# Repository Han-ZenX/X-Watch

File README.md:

# X-Watch

X-Watch 是一款开源智能手表项目，主控芯片为 **STM32L4R9AII6U**，图形界面基于 **TouchGFX** 开发。本仓库统一管理硬件设计、嵌入式固件、配套软件、文档与测试。

> 项目处于早期开发阶段（硬件 Rev1.0），接口与目录结构可能随迭代调整。

## 核心方案

| 项目 | 选型 |
|------|------|
| 主控 MCU | STM32L4R9AII6U（Arm Cortex-M4F，120 MHz，2 MB Flash，640 KB SRAM，UFBGA169） |
| 图形框架 | TouchGFX（配合 TouchGFX Designer 设计界面） |
| 图形加速 | Chrom-ART（DMA2D）、GFXMMU，显示接口可选 LTDC / MIPI DSI |
| 硬件 EDA | KiCad |
| 固件构建 | CMake + GCC ARM（arm-none-eabi） |
| 大文件管理 | Git LFS |

### 为什么选 STM32L4R9

- **超低功耗**：STM32L4+ 系列，适合电池供电的穿戴设备。
- **图形能力完整**：片上集成 LTDC、MIPI DSI Host、Chrom-ART 加速器和 GFXMMU（适合圆形屏帧缓冲），无需外置图形芯片。
- **TouchGFX 官方支持**：ST 提供 STM32L4R9I-DISCO 参考设计（圆形 AMOLED 屏），可作为软硬件起点，手册见 [docs/references/Rev1.0](docs/references/Rev1.0)。

## 目录结构

```
X-Watch/
├── firmware/      # 嵌入式固件（app / hal / drivers / services 四层架构）
├── hardware/      # 硬件设计（原理图、PCB、BOM、Gerber、3D、引脚表）
├── software/      # 配套软件（desktop / mobile / cloud）
├── tools/         # 构建脚本与辅助工具
├── docs/          # 项目文档
├── tests/         # 单元测试 / 集成测试 / 硬件在环测试
└── ci/            # CI/CD 流水线配置
```

完整的架构说明见 [docs/architecture/architecture.md](docs/architecture/architecture.md)。

## 快速开始

### 1. 获取代码

```bash
git lfs install
git clone git@github.com:Han-ZenX/X-Watch.git
```

### 2. 开发环境

- [STM32CubeMX](https://www.st.com/en/development-tools/stm32cubemx.html)：外设与时钟配置
- [TouchGFX Designer](https://www.st.com/en/development-tools/touchgfxdesigner.html)：UI 设计与代码生成
- GCC ARM 工具链（arm-none-eabi-gcc）、CMake ≥ 3.20、Ninja
- [KiCad](https://www.kicad.org/)：打开 `hardware/schematic/v1.0/XWatch_Rev1.0/` 下的工程
- 调试器：ST-LINK

### 3. 编译固件

```bash
cd firmware
cmake -B build -G Ninja -DBOARD=default
cmake --build build
```

或使用构建脚本：

```bash
python tools/scripts/build.py --board=default
```

## 硬件

- 原理图 / PCB：`hardware/schematic/v1.0/XWatch_Rev1.0/`（KiCad 工程）
- 引脚分配：[hardware/pinout/pinout.md](hardware/pinout/pinout.md)
- 每次硬件改版需同步更新引脚表与 `firmware/boards/` 下对应的板级配置。

## 开发计划

- [ ] 硬件 Rev1.0 原理图与 PCB 完成
- [ ] STM32L4R9 板级支持（时钟、电源、调试串口）
- [ ] 显示屏驱动与 TouchGFX 移植
- [ ] 触摸驱动接入
- [ ] 基础表盘与界面
- [ ] 低功耗管理

## 变更记录

见 [CHANGELOG.md](CHANGELOG.md)。

## 许可证

本项目基于 [MIT License](LICENSE) 开源。

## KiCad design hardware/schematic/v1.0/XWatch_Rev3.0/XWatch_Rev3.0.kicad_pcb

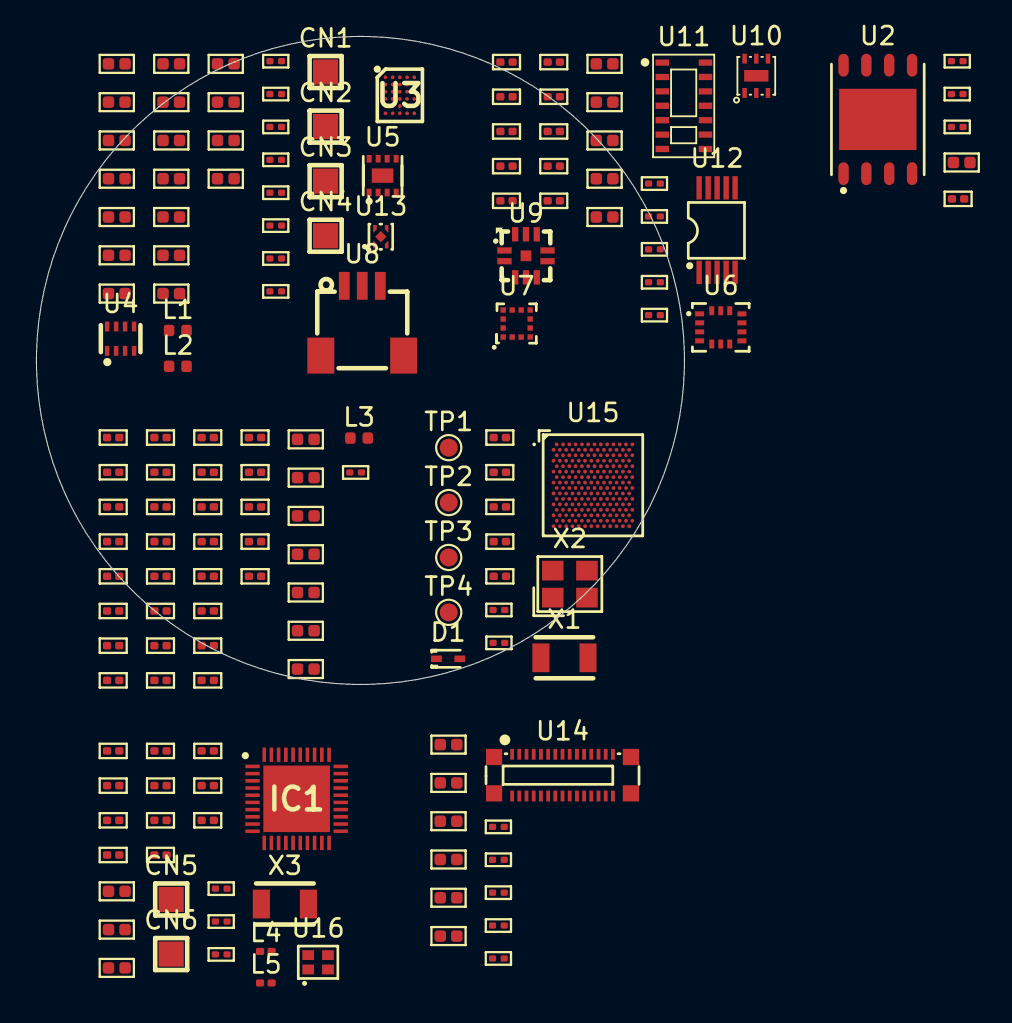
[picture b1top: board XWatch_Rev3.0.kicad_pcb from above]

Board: 2 copper layers, 36.0 x 36.0 mm, 158 parts (0 on the bottom side), 85 nets, no tracks yet.

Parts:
C1, C2, C86, C87: 5.6pF; GEN_C_0201
C3, C4: 10pF; GEN_C_0201
C5, C15, C71, C99: 4.7uF; GEN_C_0402
C6, C9, C10, C16, C17, C30, C59, C63, C78, C109: 10uF; GEN_C_0402
C7, C14, C49, C73, C75, C77: 100nF; GEN_C_0402
C8: 47nF; GEN_C_0402
C11, C12, C13, C104, C105: 2.2uF; GEN_C_0402
C18, C19, C61, C62, C64, C65, C66, C68, C74, C76, C80, C81, C101, C102: 1uF; GEN_C_0402
C20, C21, C22, C23, C24, C25, C26, C27, C28, C29, C48, C50, C51, C53, C54, C55, C56, C57, C58, C60, C67, C69, C70, C72, C79, C89, C90, C91, C92, C93, C94, C95, C96, C97, C98, C100, C103, C106, C107, C108, C110, C111, C112, C113: 100nF; GEN_C_0201
C52: 220nF; GEN_C_0201
C82: 1pF; GEN_C_0201
C83: 1.2pF; GEN_C_0201
C84, C85: 12pF; GEN_C_0201
C88: 100pF; GEN_C_0201
CN1, CN2, CN3, CN4, CN5, CN6: SCTA1A0100
D1: RB520S-30; RB520S-30_C7502701
IC1: nRF52833-QDAA-R; QFN40P500X500X90-41N
L1, L2, L3: 2.2uH; L_0402_1005Metric
L4: 4.7nH; L_0201_0603Metric
L5: 2.2nH; L_0201_0603Metric
R3, R17, R19, R26, R27, R28: 100K; GEN_R_0201
R4, R5, R13, R14: 4.7K; GEN_R_0201
R6, R7, R8, R15, R16, R18, R20, R21, R23, R24, R25: 10K; GEN_R_0201
R9: 24.9 k 1%; GEN_R_0201
R10: 38.3 k 1%; GEN_R_0201
R11, R12: 2.2K; GEN_R_0201
R22, R29: 0; GEN_R_0201
TP1, TP2, TP3, TP4: TestPoint; TestPoint_Pad_D1.0mm
U2: GD25LQ128EWIGR
U3: DA9168; BGA30C40P5X6_214X254X56
U4: TPS62840DLCR
U5: MAX17048G_T10
U6: LSM6DSOXTR
U7: LIS2MDLTR
U8: SM03B-SRSS-TB_LF_SN_P
U9: LPS27HHWTR
U10: OPT3001DNPR
U11: MAX30101EFD_T
U12: DRV2605LDGSR
U13: SK6018D4-33
U14: AXE530127-DO0143FMST02; AXE530127
U15: STM32U5A9BJY6QTR
U16: R832000033-32MHZ; R832000033
X1, X3: 32.768KHZ; NX3215SA_32_768KHZ_EXS00A-MU00525
X2: 16MHZ; TXM16M0004252CBCEO00T

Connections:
+1V8: C6.1, C20.1, C21.1, C22.1, C23.1, C24.1, C25.1, C26.1, C27.1, C28.1, C29.1, C30.1, C50.1, C51.1, C53.1, C54.1, C55.1, C56.2, C57.1, C60.1, C61.1, C67.2, C68.2, C71.1, C72.2, C75.2, C76.2, C79.2, C80.1, C89.1, C90.1, C91.1, C92.1, C93.1, C94.1, C95.1, C96.1, C97.1, C98.1, C99.1, C109.1, C110.1, C111.1, C112.1, IC1.8 (VDD_1), IC1.9 (VDDH), IC1.18 (VDD_2), IC1.30 (VDD_3), IC1.40 (VDD_4), L1.2, R4.1, R5.1, R6.1, R7.1, R11.1, R12.1, R13.1, R14.1, R15.1, R16.1, R18.1, R20.1, R21.1, R23.1, R24.1, R25.2, R28.2, R29.1, U2.8 (VCC), U4.8 (VOS), U6.5 (VDDIO), U6.8 (VDD), U6.12 (CS), U7.3 (CS), U7.9 (Vdd), U7.10 (Vdd_IO), U9.1 (Vdd_IO), U9.6 (CS), U9.10 (VDD), U10.1 (VDD), U11.11 (VDD), U14.25 (VDDIO), U15.A6 (VDD), U15.A12 (VDD), U15.A16 (VDDIO2), U15.A24 (VDD), U15.A26 (VDD), U15.B25 (VBAT), U15.E2 (VDDIO2), U15.F1 (VDD), U15.G2 (VDD), U15.G24 (VDDDSI), U15.H1 (VDD), U15.L2 (VDD), U15.L26 (VDD), U15.M1 (VDD), U15.N2 (VDD), U15.P1 (VDD), U15.R2 (VDD), U15.T1 (VDD), U15.T9 (VDDSMPS), U15.T15 (VDD), U15.T19 (VDD), U15.T25 (VDD)
+3V3: C66.1, C73.1, C74.1, C113.1, U13.1 (VOUT), U14.11 (TP_VCC), U14.23 (VCI_IN), U15.A2 (VDDUSB)
/BLE/DEC6: C81.1, IC1.26 (DEC6), IC1.38 (DEC4)
/BLE/nRESET: IC1.16 (P0.18/NRESET), R28.1
/MCU_IO/ALS_INT_N: R15.2, U10.5 (INT), U15.K21 (PF5)
/MCU_IO/BARO_INT: U9.7 (INT_DRDY), U15.L22 (PF10)
/MCU_IO/BLE_WAKE_MCU: IC1.17 (P0.20), R27.2, U15.D23 (PC13)
/MCU_IO/BLE_WAKE_NRF: IC1.7 (P0.11), R26.2, U15.T5 (PB12)
/MCU_IO/DSI_CK_N: U14.20 (MIPI_CLKN), U15.H25 (DSI_CKN)
/MCU_IO/DSI_CK_P: U14.18 (MIPI_CLKP), U15.G26 (DSI_CKP)
/MCU_IO/DSI_D0_N: U14.26 (MIPI_D0N), U15.F25 (DSI_D0N)
/MCU_IO/DSI_D0_P: U14.24 (MIPI_D0P), U15.E26 (DSI_D0P)
/MCU_IO/DSI_PWR_EN: U14.21 (PWR_EN), U15.C22 (PI5)
/MCU_IO/DSI_RESET: U14.19 (RESET), U15.E16 (PD5)
/MCU_IO/DSI_TE: U14.27 (TE), U15.N16 (PF11)
/MCU_IO/DSI_TP_INT: R20.2, U14.7 (TP_INT), U15.N14 (PE8)
/MCU_IO/DSI_TP_RESET: U14.9 (TP_RESET), U15.D21 (PI6)
/MCU_IO/HAPTIC_EN: R17.1, U12.5 (EN), U15.P17 (PF13)
/MCU_IO/I2C1.SCL: R4.2, U3.F5 (SCL), U5.7 (SCL), U15.C16 (PG14)
/MCU_IO/I2C1.SDA: R5.2, U3.E4 (SDA), U5.8 (SDA), U15.A14 (PG13)
/MCU_IO/I2C3.SCL: R12.2, U6.13 (SCL), U7.1 (SCL/SPC), U9.2 (SCL/SPC), U10.4 (SCL), U11.2 (SCL), U12.2 (SCL), U15.H15 (PH6)
/MCU_IO/I2C3.SDA: R11.2, U6.14 (SDA), U7.4 (SDA/SDI/SDO), U9.4 (SDA/SDI/SDO), U10.6 (SDA), U11.3 (SDA), U12.3 (SDA), U15.E12 (PH7)
/MCU_IO/I2C5.SCL: R14.2, U14.3 (TP_SCL), U15.F13 (PH5)
/MCU_IO/I2C5.SDA: R13.2, U14.5 (TP_SDA), U15.E10 (PH4)
/MCU_IO/IMU_INT1: U6.4 (INT1), U15.J16 (PF6)
/MCU_IO/IMU_INT2: U6.9 (INT2), U15.J14 (PF7)
/MCU_IO/MAG_DRDY: U7.7 (INT/DRDY/SDO), U15.L20 (PF9)
/MCU_IO/NRST: C48.1, TP3.1 (1_1), U15.M21 (NRST)
/MCU_IO/OSPI_CLK: U2.6 (SCLK), U15.M13 (PE10)
/MCU_IO/OSPI_IO0: U2.5 (SI(IO0)), U15.R14 (PE12)
/MCU_IO/OSPI_IO1: U2.2 (SO(IO1)), U15.N12 (PE13)
/MCU_IO/OSPI_IO2: R23.2, U2.3 (WP#(IO2)), U15.P13 (PE14)
/MCU_IO/OSPI_IO3: R25.1, U2.7 (HOLD#(IO3)), U15.R12 (PE15)
/MCU_IO/OSPI_NCS: R24.2, U2.1 (CS#), U15.P15 (PE11)
/MCU_IO/PPG_INT_N: R16.2, U11.13 (INT#), U15.T21 (PF12)
/MCU_IO/PWR_ALRT_N: R7.2, U5.5 (ALRT#), U15.C12 (PD3)
/MCU_IO/PWR_CHG_EN_N: R3.1, U3.E3 (CHG__EN_N), U15.D13 (PD2)
/MCU_IO/PWR_EN_3V3: R19.1, U13.3 (EN), U15.F15 (PD0)
/MCU_IO/PWR_INT_N: R6.2, U3.F4 (INT_N), U15.D15 (PD4)
/MCU_IO/PWR_RIN_N: C49.1, U3.D4 (RIN_N), U15.A10 (PD1)
/MCU_IO/SWCLK: TP2.1 (1_1), U15.D11 (PA14)
/MCU_IO/SWDIO: TP1.1 (1_1), U15.B3 (PA13)
/MCU_IO/USART3_CTS: IC1.14 (P0.15), U15.T7 (PB13)
/MCU_IO/USART3_RTS: IC1.15 (P0.17), U15.R6 (PB14)
/MCU_IO/USART3_RX: IC1.4 (P0.04/AIN2), U15.R10 (PB11)
/MCU_IO/USART3_TX: IC1.5 (P0.05/AIN3), U15.T13 (PB10)
/MCU_IO/USB_OTG_DM: CN3.1 (1_1), U15.C2 (PA11)
/MCU_IO/USB_OTG_DP: CN2.1 (1_1), U15.B1 (PA12)
/PWR/BAT_NTC: R9.2, R10.1, U3.D3 (TMP__SNS), U8.2 (NTC)
GND: C1.1, C2.1, C3.1, C4.2, C5.2, C6.2, C7.2, C9.2, C10.2, C11.2, C12.2, C13.2, C14.2, C15.2, C16.2, C17.2, C18.2, C19.2, C20.2, C21.2, C22.2, C23.2, C24.2, C25.2, C26.2, C27.2, C28.2, C29.2, C30.2, C48.2, C49.2, C50.2, C51.2, C52.2, C53.2, C54.2, C55.2, C56.1, C57.2, C58.2, C59.2, C60.2, C61.2, C62.2, C63.2, C64.1, C65.2, C66.2, C67.1, C68.1, C69.1, C70.2, C71.2, C72.1, C73.2, C74.2, C75.1, C76.1, C77.1, C78.1, C79.1, C80.2, C81.2, C82.2, C83.2, C84.1, C85.2, C86.1, C87.1, C88.2, C89.2, C90.2, C91.2, C92.2, C93.2, C94.2, C95.2, C96.2, C97.2, C98.2, C99.2, C100.2, C101.2, C102.2, C103.2, C104.2, C105.2, C106.2, C107.2, C108.2, C109.2, C110.2, C111.2, C112.2, C113.2, CN4.1 (1_1), CN6.1 (1_1), IC1.10 (VBUS), IC1.25 (VSS_PA), IC1.37 (VSS_1), IC1.41 (VSS_2), R3.2, R8.2, R10.2, R17.2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
unnamed: C3.2, X2.2
unnamed: C83.1, L4.2, L5.1
unnamed: CN5.1 (1_1), L5.2
unnamed: D1.2 (A), R18.2, U15.N22 (PA0)
unnamed: C82.1, IC1.24 (ANT), L4.1
unnamed: C69.2, IC1.1 (DEC1)
unnamed: C88.1, IC1.27 (DEC3)
unnamed: C70.1, IC1.21 (DEC5)
unnamed: C86.2, IC1.2 (P0.00/XL1), X3.1
unnamed: C87.2, IC1.3 (P0.01/XL2), X3.2
unnamed: C85.1, IC1.28 (XC1), U16.3
unnamed: C84.2, IC1.29 (XC2), U16.1
unnamed: C8.1, L2.1
unnamed: R9.1, U3.C5 (ILIMIT)
unnamed: C15.1, U3.C4 (REF)
unnamed: C8.2, U3.C3 (VBTS)
unnamed: C16.1, C17.1
unnamed: C12.1, U3.B5 (VOUT1)
unnamed: C13.1, U3.D5 (VOUT2)
unnamed: L1.1, U4.7 (SW)
unnamed: C52.1, U7.5 (C1)
unnamed: C64.2, U12.1 (REG)
unnamed: R21.2, U14.6 (CS)
unnamed: R22.2, U14.12 (SDO_SDI1)
unnamed: C100.1, C101.1, C102.1, C103.1, R29.2, U15.P25 (VREF+), U15.R26 (VDDA)
unnamed: L3.2, U15.T11 (VLXSMPS)
unnamed: C1.2, U15.C26 (PC14-OSC32_IN), X1.1
unnamed: C2.2, U15.D25 (PC15-OSC32_OUT), X1.2
unnamed: C4.1, U15.M23 (PH0-OSC_IN), X2.1 (OSC1)
unnamed: U15.M25 (PH1-OSC_OUT), X2.3 (OSC2)
unnamed: R8.1, U15.E20 (PH3-BOOT0)
VBAT: C7.1, C11.1, C14.1, C62.1, C63.1, U3.F3 (VBAT__SNS), U5.2 (CELL), U5.3 (VDD), U8.1 (BAT+), U12.6 (VDD/NC), U12.10 (VDD)
VBUS: C18.1, C19.1, CN1.1 (1_1), U3.A5 (VBUS__SNS)
VCORE: C104.1, C105.1, C106.1, C107.1, C108.1, L3.1, U15.A4 (VDD11), U15.A22 (VDD11), U15.D1 (VDD11USB), U15.J24 (VDD11DSI), U15.T3 (VDD11)
VSYS: C5.1, C9.1, C10.1, C58.1, C59.1, C65.1, C77.2, C78.2, L2.2, U4.2 (VIN), U4.4 (EN), U11.9 (VLED+), U11.10 (VLED+), U13.4 (VIN), U14.29 (VBAT), U14.30 (VBAT)

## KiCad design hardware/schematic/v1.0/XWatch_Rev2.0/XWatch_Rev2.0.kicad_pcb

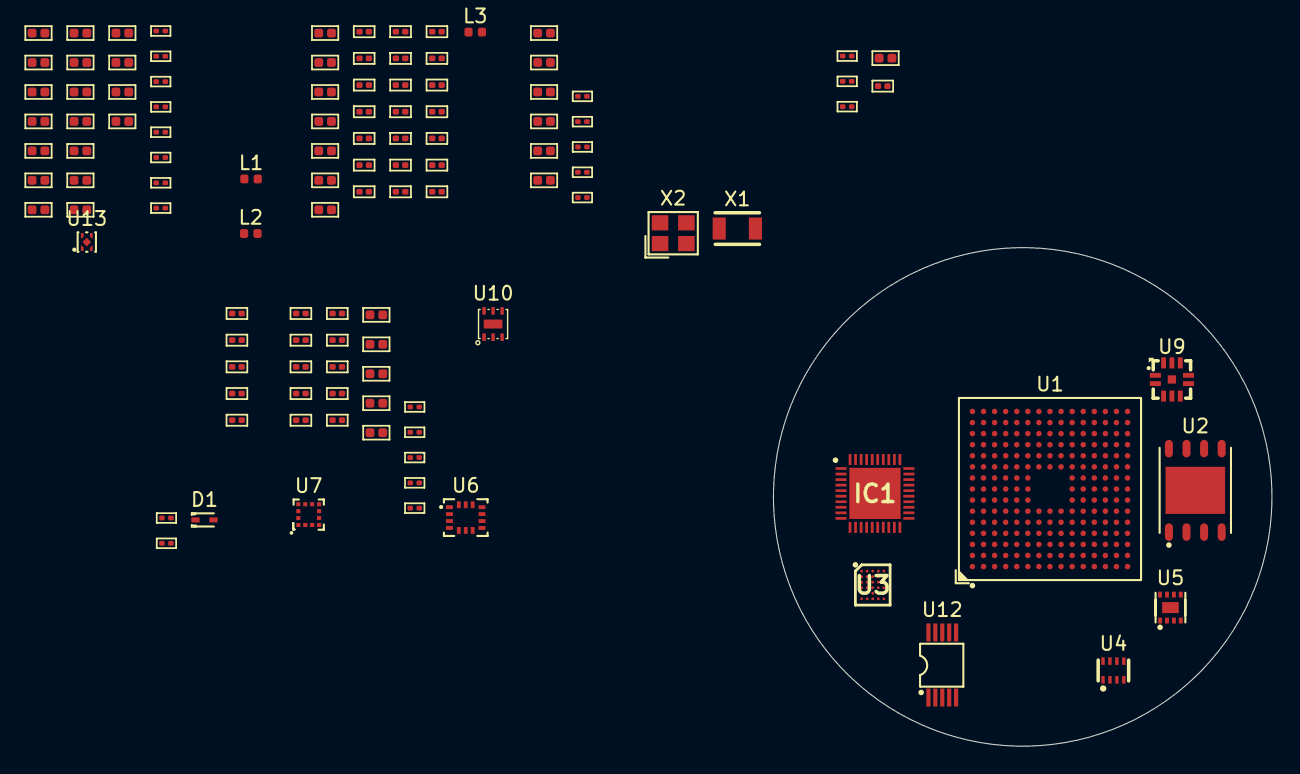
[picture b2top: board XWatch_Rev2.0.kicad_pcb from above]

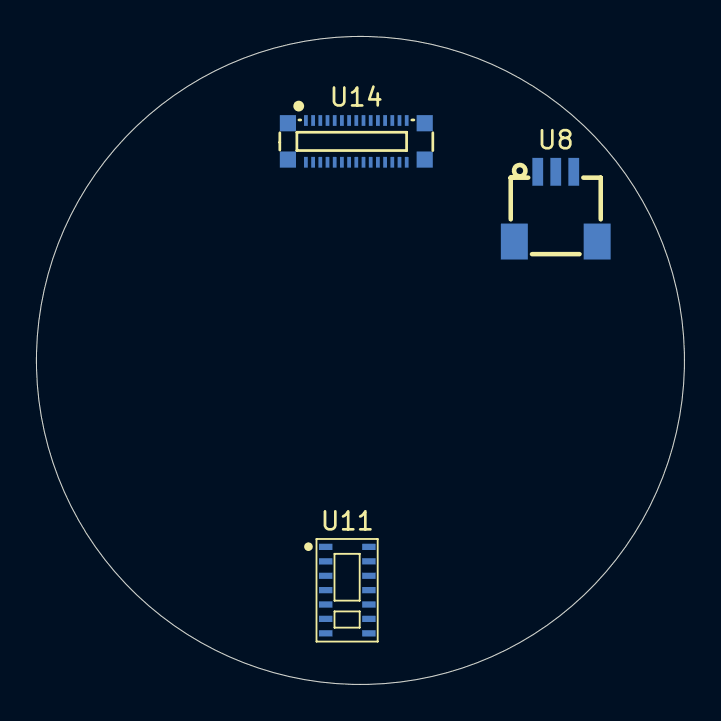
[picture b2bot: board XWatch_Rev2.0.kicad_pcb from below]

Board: 2 copper layers, 36.0 x 36.0 mm, 118 parts (3 on the bottom side), 48 nets, no tracks yet.

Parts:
C1, C2: 5.6pF; GEN_C_0201
C3, C4: 10pF; GEN_C_0201
C5, C15, C33: 4.7uF; GEN_C_0402
C6, C9, C10, C16, C17, C30, C46, C59, C63, C78: 10uF; GEN_C_0402
C7, C14, C49, C73, C75, C77: 100nF; GEN_C_0402
C8: 47nF; GEN_C_0402
C11, C12, C13, C41, C42: 2.2uF; GEN_C_0402
C18, C19, C34, C36, C61, C62, C64, C65, C66, C68, C74, C76: 1uF; GEN_C_0402
C20, C21, C22, C23, C24, C25, C26, C27, C28, C29, C31, C32, C35, C37, C38, C39, C40, C43, C44, C45, C47, C48, C50, C51, C53, C54, C55, C56, C57, C58, C60, C67: 100nF; GEN_C_0201
C52: 220nF; GEN_C_0201
D1: RB520S-30; RB520S-30_C7502701
IC1: nRF52833-QDAA-R; QFN40P500X500X90-41N
L1, L2, L3: 2.2uH; L_0402_1005Metric
R3, R17, R19: 100K; GEN_R_0201
R4, R5, R13, R14: 4.7K; GEN_R_0201
R6, R7, R8, R15, R16, R18, R20, R21, R23, R24, R25: 10K; GEN_R_0201
R9: 24.9 k 1%; GEN_R_0201
R10: 38.3 k 1%; GEN_R_0201
R11, R12: 2.2K; GEN_R_0201
R22: 0; GEN_R_0201
U1: STM32U5G9NJH6Q
U2: GD25LQ128EWIGR
U3: DA9168; BGA30C40P5X6_214X254X56
U4: TPS62840DLCR
U5: MAX17048G_T10
U6: LSM6DSOXTR
U7: LIS2MDLTR
U8: SM03B-SRSS-TB_LF_SN_P
U9: LPS27HHWTR
U10: OPT3001DNPR
U11: MAX30101EFD_T
U12: DRV2605LDGSR
U13: SK6018D4-33
U14: AXE530127-DO0143FMST02; AXE530127
X1: 32.768KHZ; NX3215SA_32_768KHZ_EXS00A-MU00525
X2: 16MHZ; TXM16M0004252CBCEO00T

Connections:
+1V8: C6.1, C20.1, C21.1, C22.1, C23.1, C24.1, C25.1, C26.1, C27.1, C28.1, C29.1, C30.1, C31.1, C32.1, C33.1, C38.1, C39.1, C40.1, C46.1, C47.1, C50.1, C51.1, C53.1, C54.1, C55.1, C56.2, C57.1, C60.1, C61.1, C67.2, C68.2, C75.2, C76.2, L1.2, R4.1, R5.1, R6.1, R7.1, R11.1, R12.1, R13.1, R14.1, R15.1, R16.1, R18.1, R20.1, R21.1, R23.1, R24.1, R25.2, U1.C2 (VBAT), U1.E8 (VDDIO2), U1.E9 (VDDUSB), U1.F5 (VDD), U1.F8 (VDD), U1.G5 (VDDDSI), U1.G11 (VDDIO2), U1.H11 (VDD), U1.J5 (VDD), U1.J11 (VDD), U1.K11 (VDD), U1.L7 (VDD), U1.L8 (VDD), U1.L9 (VDD), U1.L11 (VDD), U1.R12 (VDDSMPS), U2.8 (VCC), U4.8 (VOS), U6.5 (VDDIO), U6.8 (VDD), U6.12 (CS), U7.3 (CS), U7.9 (Vdd), U7.10 (Vdd_IO), U9.1 (Vdd_IO), U9.6 (CS), U9.10 (VDD), U10.1 (VDD), U11.11 (VDD), U14.25 (VDDIO)
+3V3: C66.1, C73.1, C74.1, U13.1 (VOUT), U14.11 (TP_VCC), U14.23 (VCI_IN)
/DSI_LCD/TP_INT: R20.2, U14.7 (TP_INT)
/DSI_LCD/TP_SCL: R14.2, U14.3 (TP_SCL)
/DSI_LCD/TP_SDA: R13.2, U14.5 (TP_SDA)
/MEMORY/OSPI_IO2: R23.2, U2.3 (WP#(IO2))
/MEMORY/OSPI_IO3: R25.1, U2.7 (HOLD#(IO3))
/MEMORY/OSPI_NCS: R24.2, U2.1 (CS#)
/PWR/BAT_NTC: R9.2, R10.1, U3.D3 (TMP__SNS), U8.2 (NTC)
/PWR/EN_3V3: R19.1, U13.3 (EN)
/PWR/FG_ALRT_N: R7.2, U5.5 (ALRT#)
/PWR/PWR_CHG_EN_N: R3.1, U3.E3 (CHG__EN_N)
/PWR/PWR_INT_N: R6.2, U3.F4 (INT_N)
/PWR/PWR_RIN_N: C49.1, U3.D4 (RIN_N)
/PWR/PWR_SCL: R4.2, U3.F5 (SCL), U5.7 (SCL)
/PWR/PWR_SDA: R5.2, U3.E4 (SDA), U5.8 (SDA)
/SENSOR/ALS_INT_N: R15.2, U10.5 (INT)
/SENSOR/DRV_REG: C64.2, U12.1 (REG)
/SENSOR/HAPTIC_EN: R17.1, U12.5 (EN)
/SENSOR/MAG_C1: C52.1, U7.5 (C1)
/SENSOR/PPG_INT_N: R16.2, U11.13 (INT#)
/SENSOR/SENSOR_SCL: R12.2, U6.13 (SCL), U7.1 (SCL/SPC), U9.2 (SCL/SPC), U10.4 (SCL), U11.2 (SCL), U12.2 (SCL)
/SENSOR/SENSOR_SDA: R11.2, U6.14 (SDA), U7.4 (SDA/SDI/SDO), U9.4 (SDA/SDI/SDO), U10.6 (SDA), U11.3 (SDA), U12.3 (SDA)
GND: C1.1, C2.1, C3.1, C4.2, C5.2, C6.2, C7.2, C9.2, C10.2, C11.2, C12.2, C13.2, C14.2, C15.2, C16.2, C17.2, C18.2, C19.2, C20.2, C21.2, C22.2, C23.2, C24.2, C25.2, C26.2, C27.2, C28.2, C29.2, C30.2, C31.2, C32.2, C33.2, C34.2, C35.2, C36.2, C37.2, C38.2, C39.2, C40.2, C41.2, C42.2, C43.2, C44.2, C45.2, C46.2, C47.2, C48.2, C49.2, C50.2, C51.2, C52.2, C53.2, C54.2, C55.2, C56.1, C57.2, C58.2, C59.2, C60.2, C61.2, C62.2, C63.2, C64.1, C65.2, C66.2, C67.1, C68.1, C73.2, C74.2, C75.1, C76.1, C77.1, C78.1, R3.2, R8.2, R10.2, R17.2, R19.2, R22.1, U1.A1 (VSS), U1.A15 (VSS), U1.E10 (VSS), U1.F6 (VSS), U1.F7 (VSS), U1.F9 (VSS), U1.F10 (VSS), U1.G6 (VSSDSI), U1.G10 (VSS), U1.H2 (VSSDSI), U1.H6 (VSSDSI), U1.H10 (VSS), U1.H15 (VSS), U1.J2 (VSSDSI), U1.J6 (VSS), U1.J10 (VSS), U1.J15 (VSS), U1.K5 (VREFM), U1.K6 (VSSA), U1.K7 (VSS), U1.K8 (VSS), U1.K9 (VSS), U1.K10 (VSS), U1.L10 (VSS), U1.P12 (VSSSMPS), U1.R1 (VSS)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
unnamed: C3.2, X2.2
unnamed: D1.2 (A), R18.2, U1.N4 (PA0-WKUP1)
unnamed: C34.1, C35.1, C36.1, C37.1, U1.L5 (VREFP), U1.L6 (VDDA)
unnamed: L3.2, U1.R11 (VLXSMPS)
unnamed: C48.1, U1.R2 (NRST)
unnamed: C2.2, U1.B1 (PC14-OSC32_IN), X1.2
unnamed: C1.2, U1.C1 (PC15-OSC32_OUT), X1.1
unnamed: U1.N1 (PH0-OSC_IN), X2.3 (OSC2)
unnamed: C4.1, U1.N2 (PH1-OSC_OUT), X2.1 (OSC1)
unnamed: R8.1, U1.B4 (PH3-BOOT0)
unnamed: C8.1, L2.1
unnamed: R9.1, U3.C5 (ILIMIT)
unnamed: C15.1, U3.C4 (REF)
unnamed: C8.2, U3.C3 (VBTS)
unnamed: C16.1, C17.1
unnamed: C12.1, U3.B5 (VOUT1)
unnamed: C13.1, U3.D5 (VOUT2)
unnamed: L1.1, U4.7 (SW)
unnamed: R21.2, U14.6 (CS)
unnamed: R22.2, U14.12 (SDO_SDI1)
VBAT: C7.1, C11.1, C14.1, C62.1, C63.1, U3.F3 (VBAT__SNS), U5.2 (CELL), U5.3 (VDD), U8.1 (BAT+), U12.6 (VDD/NC), U12.10 (VDD)
VBUS: C18.1, C19.1, U3.A5 (VBUS__SNS)
VDD11: C41.1, C42.1, C43.1, C44.1, C45.1, L3.1, U1.E6 (VDD11), U1.E11 (VDD11), U1.F11 (VDD11USB), U1.H5 (VDD11DSI), U1.R13 (VDD11)
VSYS: C5.1, C9.1, C10.1, C58.1, C59.1, C65.1, C77.2, C78.2, L2.2, U4.2 (VIN), U4.4 (EN), U11.9 (VLED+), U11.10 (VLED+), U13.4 (VIN), U14.29 (VBAT), U14.30 (VBAT)

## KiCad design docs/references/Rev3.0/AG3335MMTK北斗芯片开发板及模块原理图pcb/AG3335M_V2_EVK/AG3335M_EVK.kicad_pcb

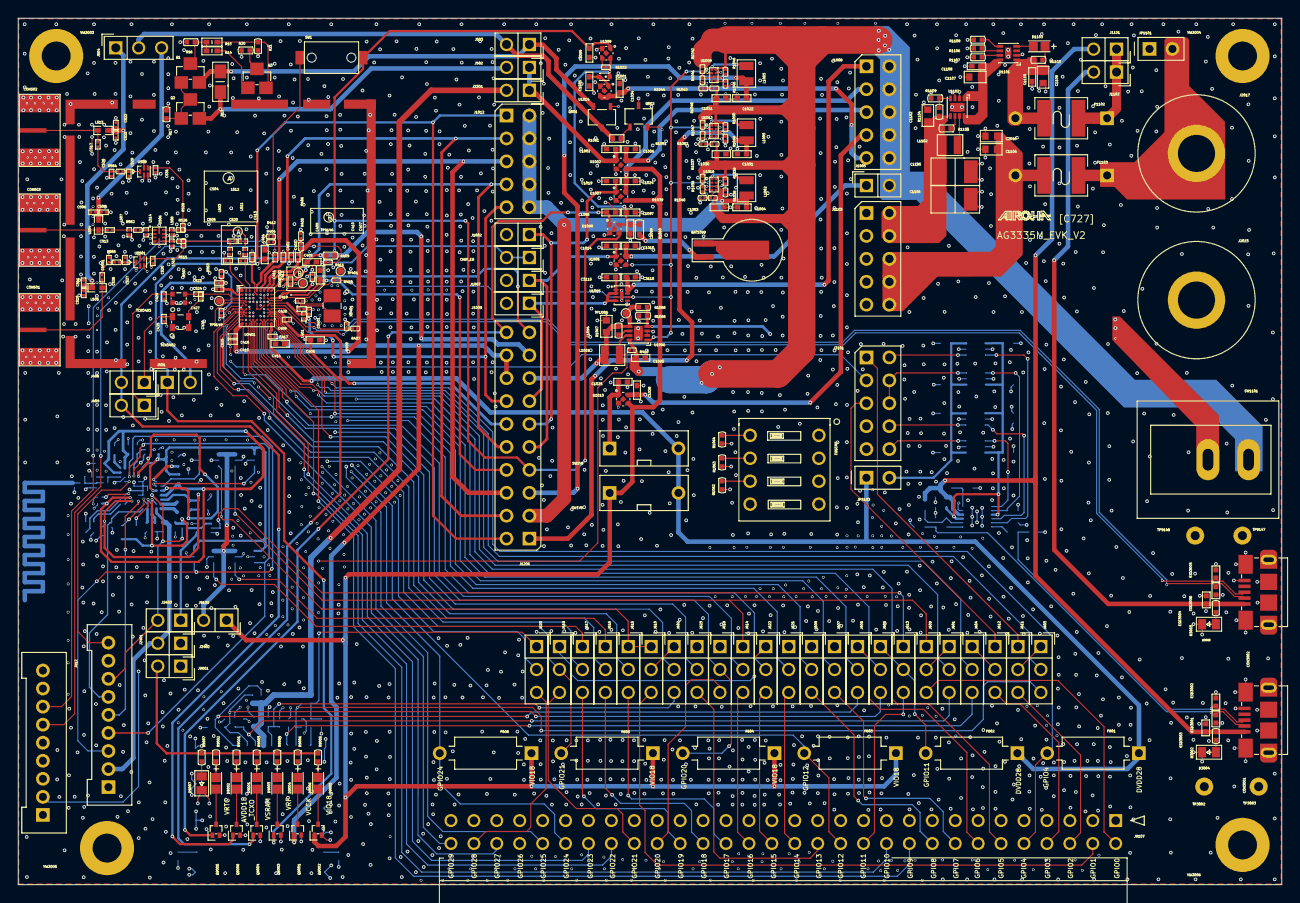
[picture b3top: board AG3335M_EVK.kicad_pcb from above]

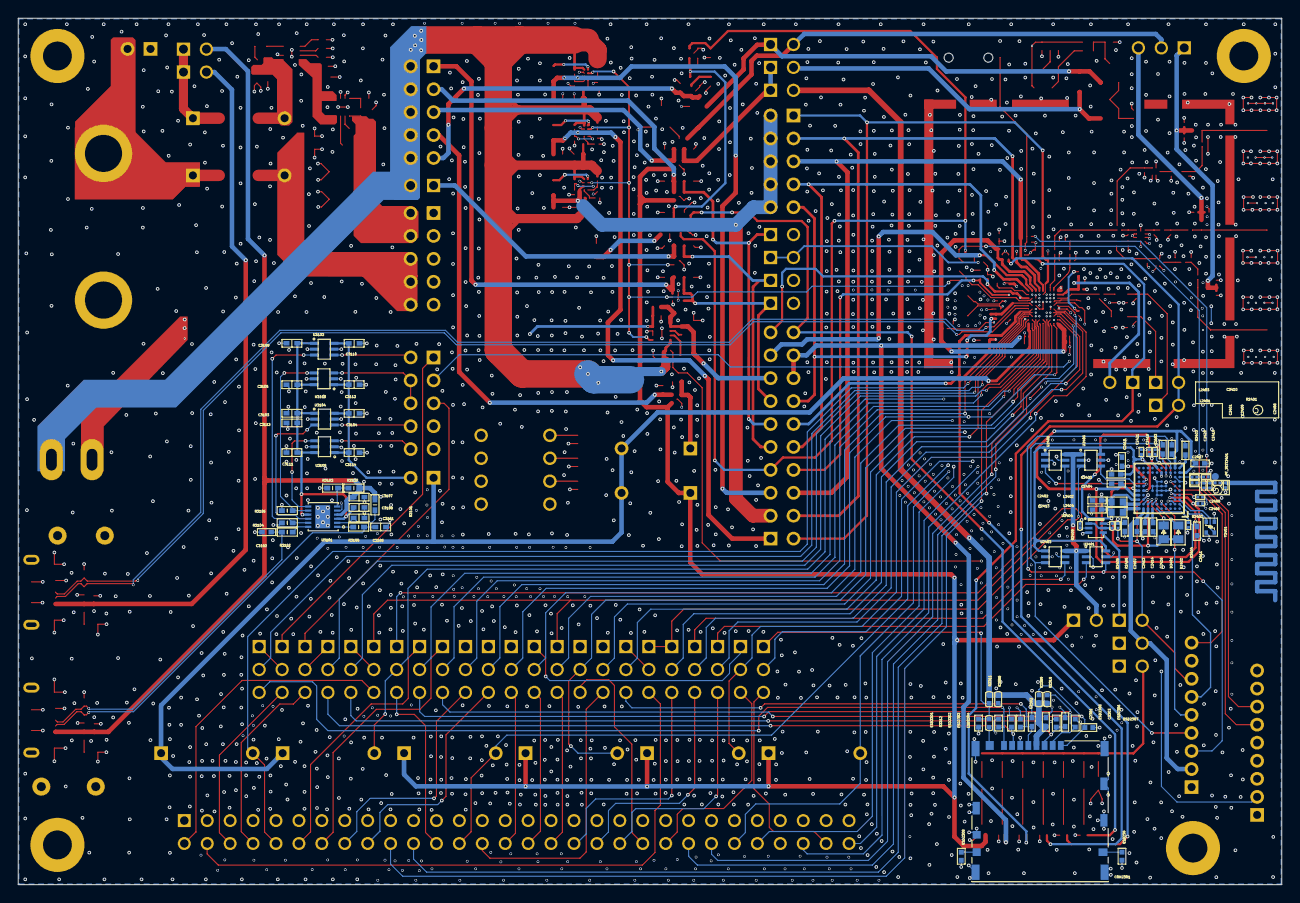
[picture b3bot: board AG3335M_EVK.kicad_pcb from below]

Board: 4 copper layers, 140.0 x 96.0 mm, 381 parts (86 on the bottom side), 241 nets.

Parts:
BAT1099: C0.22F3.3V$2F$SMD$2F$EN-RL
C0401, C402, C403, C407, C408, C409, C411, C412, C413, C415, C416, C417, C419, C420, C425, C426, C427, C428, C0501, C504, C505, C506, C508, C510, C511, C513, C517, C520, C521, C522, C523, C524, C525, C526, C527, C528, C529, C530, C531, C2401, C2405, C2406, C2408, C2409, C2410, C2418, C2421: C0201
C404, C405, C406, C410, C414, C1002, C1003, C1004, C1006, C1014, C1015, C1019, C1021, C1022, C1024, C1025, C1028, C1030, C1031, C1034, C1035, C1095, C1096, C1097, C1098, C1099, C1108, C1110, C2301, C2302, C2303, C2402, C2403, C2404, C2407, C2411, C2412, C2413, C2414, C2415, C2416, C2417, C2419, C2420, C3102, C3115, C3116: C0402
C1094, C1102, C1104, C1107, C1109, C2016: C0603
C1105, C1106: C1210
C3101, C3103, C3104, C3105, C3106, C3107, C3108, C3109, C3110, C3111, C3112, C3113, C3114: SC0402
CHIP_EN: DIP2$2F$P2.54
CON501, CON502, CON503: SMA8400M
CON2301: MICROSD$2F$8P$2F$SMD$2F$TA-M017-012-07-811
CON3001, CON3002: MICROUSB$2F$5P$2F$SMD$2F$P0.65$2F$R$2F$8791-N005-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; MICROUSB$2F$5P$2F$SMD$2F$P0.65$2F$R$2F$8791-N005-M1A0
D1001: D$2F$SMD$2F$VMD2
D1103, D9001, D9002, D9003, D9004, D9005, D9006: LED190
D2401, D2402, D3004, D3005, D9007: LED-S
ESD239, ESD2301, ESD2302, ESD2303, ESD2304, ESD2305, ESD2306, ESD2307, ESD2308, ESD3001, ESD3002, ESD3003, ESD3004, ESD3005, ESD3006: VR0402
F601, F602, F603, F604, F605, F606: R$5C$DIP
F1102, F1103: FUSE$2F$DIP$2F$SMD
J408, J409, J501, J502, J503, J1002, J1005, J1007, J1009, J1101, J1102, J2301, J2402, J2403, J9001, J9109: DIP2$2F$P2.54
J412, J2401: SIP-9P-2MM-FRAME
J504, J601, J602, J603, J604, J605, J606, J607, J608, J609, J610, J611, J612, J613, J614, J615, J616, J617, J618, J619, J620, J621, J622, J623: DIP3$2F$P2.54
J1008, J1012, J1103, J3101: HEADER10
J1206: HEADER10X2-P2.54
J2017, J2023: JACK$2F$BANAAA
J9107: DIP30X2$2F$P2.54$2F$R$2F$PHR230GB138
JP1101, JP3103: SIP-2P
L401, L503, L507, L508, L511, L512, L514, L515: L0201
L504, L505, L513: L$2F$IND$2F$SMD$2F$0402
L1001, L1102: L$2F$IND$2F$SMD$2F$2520
L1002, L1003, L1005: L$2F$IND$2F$SMD$2F$LQM2MP-0806
L2401, L2403: C0201
L2402, L2404: C0603_H300
PF_TEST2401: PADCB
Q1, Q2, Q3: SOT-23
Q501, Q502: SPP2301_USI
Q9001, Q9002, Q9003, Q9004, Q9005, Q9006: 2-1L1B$2F$SMD$2F$SSM3K35MFV
R13: R0805
R14, R15, R3101, R3102, R3103, R3104, R3105, R3106, R3107: SR0402
R16, R17, R20, R21, R409, R1062, R1063, R1064, R1065, R1067, R1068, R1103, R1104, R1105, R1106, R1107, R1108, R1109, R2308, R2309, R2310, R2311, R2312, R3002, R3003, R9001, R9002, R9003, R9004, R9005, R9006, R9007: R0402
R404, R405, R406, R407, R408, R410, R411, R412, R413, R507, R511, R526, R528, R552, R553, R554, R555, R1033, R1035, R1036, R1037, R1038, R1039, R1040, R1041, R1042, R1043, R1044, R1045, R1046, R1047, R1048, R1049, R1050, R1051, R1052, R2401, R2405, R2406, R2409: R0201
R1060: R0402$2F$SMD
R1061: 0402_USI
R2402, R2404: C0201
R2403: C0402
SHORT402: NC$2F$MMD$2F$L1$2F$4MIL
SW1: TS6301E180G
SW1V8, SW2V8: DIP-SWITCH_2X1
SW1101: SW2P$2F$DIP-V1
SW2002: SW8P_DIP_P2.54
TCXO402: TXCO4P$2F$SMD$2F$P0.4$2F$2.0X1.6$2F$KT2016K
TCXO403: TXCO4P$2F$SMD$2F$P0.4$2F$1.65X1.25$2F$1612TCXO
TP401, TP1001, TP9146, TP9149: TP30MIL
TP3002, TP3003, TP9147, TP9148: HOLE$2F$PTH$2F$D1R2
U0401: AG3335M_3.8X4.2(R9XC10)-0.4BPAA
U0501, U509: SAW-1.1X0.9
U506: SAW1511
U1002, U1005, U1007, U1010, U1014, U1098, U1099: ZQFN-4L-1X1
U1008, U1012, U1016: WL-CSP0.9X1.6-8
U1015: XDFN8-P0.4-1.6X1.2
U1096, U1102: WDFN8$2F$SMD$2F$P0.5$2F$RT5715
U1101: WDFN8$2F$SMD$2F$P0.5$2F$RT9718
U2401, U2403, U2405, U2406, U3102, U3103, U3104, U3105: SOT363-6PIN
U2402: BGA76-5.5X5.5-AHT
U2404: EMT6-P0.5
U3101: DFN12
VIA3003, VIA3004, VIA3005, VIA3006: TH3MM
X0401: RTC3215
Y2401: XT2016

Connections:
1V8_LDO: C1004.1, J1012.2, J1012.4, J1012.6, J1012.8, J1012.10, J1206.3, L1002.2, U1016.C2
2V8_LDO: C1025.1, SW2V8.1, U1010.1
3V1_LDO_RTC: C1035.1, D1001.1, U1014.1
3V3_LDO_ANT: J503.1, Q1.2, Q501.2, R13.2
3V3_LDO_IC: C1002.1, J502.1, J2301.1, U1002.1
3V3_LDO_RF: J502.2, Q2.2, R13.1
3V3_LDO_SD: C2301.1, CON2301.4, J2301.2, R2308.2, R2309.2, R2310.2, R2311.1
AD_IN: C1102.1, C1105.1, C1106.1, J1103.2, J1103.4, L1102.2, R1104.1, R1105.2, U1102.5
AD_IN_FB: R1104.2, R1109.1, U1102.4
AD_IN_PG: R1105.1, U1102.6
AD_IN_PIN: C1107.1, C1108.1, U1101.8, U1102.1, U1102.8
AG3335_GPIO0_O: J609.3, J9107.2
AG3335_GPIO1_O: J610.3, J9107.4
AG3335_GPIO2_O: J611.3, J9107.6
AG3335_GPIO3_O: J612.3, J9107.8
AG3335_GPIO4_O: F601.2, J9107.10
AG3335_GPIO5_O: J605.1, J9107.12
AG3335_GPIO6_O: J606.1, J9107.14
AG3335_GPIO7_O: J607.3, J9107.16
AG3335_GPIO8_O: J608.3, J9107.18
AG3335_GPIO11: F602.2, J613.2
AG3335_GPIO11_O: J613.3, J9107.24
AG3335_GPIO12_O: F603.2, J9107.26
AG3335_GPIO13_O: J623.3, J9107.28
AG3335_GPIO14_O: J621.3, J9107.30
AG3335_GPIO15_O: J622.3, J9107.32
AG3335_GPIO16_O: J614.3, J9107.34
AG3335_GPIO17_O: J615.3, J9107.36
AG3335_GPIO18_O: J616.3, J9107.38
AG3335_GPIO19_O: J617.3, J9107.40
AG3335_GPIO20: F604.2, J618.2
AG3335_GPIO20_O: J618.3, J9107.42
AG3335_GPIO21: F605.2, J619.2
AG3335_GPIO21_O: J619.3, J9107.44
AG3335_GPIO24_O: F606.2, J9107.50
AG3335_GPIO26_O: J3101.3, J9107.54
AG3335_GPIO28_O: J620.3, J9107.58
ANTENNA_BIAS: J618.1, J623.1, Q501.1
ANT_DETECT: J621.1, Q3.2, R15.2, R21.2
AVDD07_DCXO: C525.1, R553.1
AVDD07_L1_L5: C523.1, C524.1, J501.2, R553.2
AVDD18_IN_IC: C412.1, J1012.3, J1206.4
AVDD18_TCXO: C402.1, J408.2, J409.2, Q9006.1
AVDD18_USB: C3115.1, J1009.1, J1206.13, U1015.1, U1015.2, U1015.4
AVDD18_USB_IC: C0401.1, L401.1
AVDD18_USB_L: J1012.9, J1206.14, L401.2
AVSS_AUXADC: C409.2, SHORT402.2
BATP: C2412.1, J2401.2, J2402.2, U2402.A9
BATP_35: J412.2, R410.1
BA_IN: C1104.1, C2016.1, F1103.2, J1103.6, J1103.8, J1103.10
BTEN: J613.1, R2409.1, R2409.2, U2404.2
BUCK_LV: C2413.1, C2418.1, L2404.2, U2402.E10, U2402.J5
BUCK_MV: C2402.1, C2411.1, L2402.2, U2402.B2, U2402.C10
CHIP_EN: CHIP_EN.1, CHIP_EN.2, R409.2, R411.2
COIN_BATTERY_IN: C1097.1, C1098.1, D1001.2, R1033.2, R1060.2, U1098.4, U1099.4
DVDD28_IO: C417.1, F601.1, F602.1, JP3103.1, SW1V8.2, SW2V8.2
EINT_ANTENNA: J619.1, J622.1, Q502.2
EXT_PWR_EN: R413.2, U1005.3, U1008.B1, U1012.B1, U1015.6, U1016.B1, U1096.1
EXT_PWR_EN_IC: R413.1, TP401.1
EXT_VCORE: C1094.1, J1206.15, L1001.2, R1067.2, R1068.1, TP1001.1, U1096.5
FSOURCE_D: R407.1, R408.2
FT234XD_CTS: R3104.2, U3101.11, U3102.3
FT234XD_RTS: R3106.2, U3101.8, U3103.4
FT234XD_RX: U3101.10, U3104.3
FT234XD_TX: U3101.7, U3105.4
FT234XD_VCCIO: C3103.2, C3106.2, C3108.1, C3109.2, C3111.2, C3113.2, U3101.3, U3101.9, U3102.1, U3103.6, U3104.1, U3105.6
GND_POWER: BAT1099.2, C0401.2, C402.2, C403.2, C404.2, C405.2, C406.2, C407.2, C408.2, C410.2, C411.2, C412.2, C413.2, C414.2, C415.2, C416.2, C417.2, C419.2, C420.2, C425.2, C428.2, C504.2, C505.2, C506.1, C508.2, C510.1, C511.2, C520.2, C521.1, C522.2, C523.2, C524.2, C525.2, C526.2, C527.2, C528.2, C529.2, C530.2, C531.2, C1002.2, C1003.2, C1004.2, C1006.2, C1014.2, C1015.2, C1019.2, C1021.2, C1022.2, C1024.2, C1025.2, C1028.2, C1030.2, C1031.2, C1034.2, C1035.2, C1094.2, C1095.2, C1096.2, C1097.2, C1098.2, C1099.2, C1102.2, C1104.2, C1105.2, C1106.2, C1107.2, C1108.2, C1109.2, C1110.2, C2016.2, C2301.2, C2302.2, C2303.2, C2401.1, C2402.2, C2403.1, C2404.1, C2405.1, C2406.1, C2407.1, C2408.2, C2409.1, C2410.1, C2411.2, C2412.2, C2413.2, C2414.2, C2415.1, C2416.2, C2417.1, C2418.2, C2419.1, C2420.1, C2421.2, C3101.2, C3102.2, C3103.1, C3104.1, C3105.1, C3106.1, C3107.1, C3108.2, C3109.1, C3110.1, C3111.1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
HV_MIC: C2416.1, U2402.A7
LDO_LV: C2415.2, U2402.G9
LDO_LV2: C2404.2, C2406.2, C2417.2, C2420.2, U2402.C2, U2402.D10, U2402.J1, U2402.K2
LED0: D2401.C, U2402.B8
LED1: D2402.C, U2402.B7
MSDC_SD_CLK_SD: C2302.1, CON2301.5, ESD2304.2, J602.3
MSDC_SD_CMD_SD: C2303.1, CON2301.3, ESD2305.2, J601.3
MSDC_SD_DAT0_SD: CON2301.7, ESD2303.2, J604.3
MSDC_SD_DAT1_SD: CON2301.8, ESD2302.2, J603.3, R2308.1
MSDC_SD_DAT2_SD: CON2301.1, ESD2307.2, J606.3, R2309.1
MSDC_SD_DAT3_SD: CON2301.2, ESD2306.2, J605.3, R2310.1
N51633: CON2301.9, ESD239.2
N52123: CON2301.12, R2312.1
N16794950: L1003.1, U1008.A1
N16795229: L1005.1, U1012.A1
N16854862: D9001.1, R9001.1
N16854864: J9001.2, R9001.2, R9002.2, R9003.2, R9004.2, R9005.2, R9006.2, R9007.2
N16854870: D9001.2, Q9006.3
N16854891: D9004.2, Q9003.3
N16854903: D9003.1, R9003.1
N16854911: D9005.2, Q9002.3
N16854913: D9006.1, R9006.1
N16854915: D9005.1, R9005.1
N16854917: D9002.1, R9002.1
N16854919: D9004.1, R9004.1
N16854923: D9002.2, Q9005.3
N16854939: D9003.2, Q9004.3
N16854943: D9006.2, Q9001.3
N16870677: L2402.1, U2402.B10
N16870742: C2405.2, U2402.D2
N16870865: L2404.1, U2402.A10
N17202749: C530.1, R507.2, U0501.4
N17206048: C504.1, L503.2, R507.1, R511.1
N17206944: C531.1, R528.1, U509.4
N17207071: L511.2, L512.1, R526.2, R528.2
N17484756: D3004.A, R3002.2
N17605947: C513.2, L507.1, R552.1
N17609220: L515.1, R511.2, U506.6
N17612681: C0501.2, C526.1, R555.2
N17616255: C517.2, C528.1, R554.2
N17980673: L508.1, R526.1, U506.9
N18225807: R3102.1, U3101.12
N18225821: R3103.2, R3107.2, U3101.6
N18225837: R3105.1, U3101.1
N18225847: C3101.1, R3101.2, U3101.2
N18232969: D1103.1, R1103.2
N18233257: L1102.1, U1102.7
N18234980: F1102.1, J1101.1, J1102.1
N18236556: J1103.1, J1103.3, J1103.5, J1103.7, J1103.9, SW1101.1
N18250230: C2408.1, R2401.1
N18250379: C2410.2, L2403.2
N18285237: L514.1, R552.2, U506.1
N18322393: R2405.1, U2404.1, U2404.5
N18322505: J2403.1, U2404.4
N18335230: R1033.1, U1099.3
N18349170: BAT1099.1, R1060.1
N18407213: D3005.A, R3003.2
N18420282: F1103.1, J2017.1, JP1101.2
N18427771: C527.1, R555.1, U0501.1
N18429529: C529.1, R554.1, U509.1
N18461729: R1065.1, R1068.2, SW2002.1, SW2002.2, SW2002.3, U1096.4
N18461746: R1063.1, SW2002.6
N18461748: R1062.1, SW2002.7
N18461760: R1064.1, SW2002.5
N18461961: L1001.1, U1096.7
N18461975: R1067.1, U1096.6
N18466194: J601.1, J609.2
N18468488: J602.1, J610.2
N18468512: J603.1, J611.2
N18468536: J604.1, J612.2
N18508343: J412.7, R412.1
N18512158: Q1.1, Q2.1, Q2.3, R17.2
N18512190: Q1.3, R14.1, R15.1, R16.2
N18512210: Q3.1, R14.2
N18512260: Q3.3, R20.2
N18512651: J503.2, J504.2, Q501.3, R1061.1
N18512653: Q502.1, R1061.2
N18539579: L1002.1, U1016.A1
N184205860: D9007.A, R9007.1
OD_GPIO: J2401.5, U2402.B5
OSC_XIN: C426.1, C427.1
OVP_EN#: R1108.1, U1101.5
OVP_ILIM: R1107.1, U1101.7
OVP_VB: R1106.1, U1101.6
OVP_WRN#: D1103.2, U1101.4
PIO1: J2401.9, U2402.G2
PIO28: R2402.1, U2402.J4
PIO29: R2402.2, R2403.1, U2402.K4
PWR_PWR_EN: R404.2, R412.2, SW1.2
REGEN: J2401.7, J2403.2, R2406.1, U2402.C9
RF: C2401.2, C2409.2, L2401.2, PF_TEST2401.1, R2401.2
RF_IN_L1: C505.1, L503.1
RF_IN_L5: C520.1, L511.1
RF_P: L2401.1, L2403.1, U2402.H1
RST_N: J2401.6, R2404.2, U2402.A6
RST_N_35: J412.6, R411.1
RTC_XIN: C419.1, X0401.1
RTC_XOUT: C420.1, X0401.2
SDCD_SD_IC: ESD2301.2, J620.1, R2311.2, R2312.2
SYSTEM_PWRIN: C1109.1, C1110.1, F1102.2, R1103.1, U1101.1
TCXO_1612_VCC: C428.1, J409.1, TCXO403.4
TCXO_2016_VCC: C425.1, J408.1, TCXO402.4
TESTMODE: R405.1, R406.2
TXC_1612_OUT: C427.2, TCXO403.3
TXC_2016_OUT: C426.2, TCXO402.3
UART0_CTS: J612.1, J3101.5
UART0_RTS: J611.1, J3101.1
UART0_RX_AG3335: J412.4, J608.1, J3101.9
UART0_TX_AG3335: J412.3, J607.1, J3101.7
UART2_CTS: J610.1, J615.1, U2405.3
UART2_RTS: J609.1, J614.1, U2406.4
UART2_RX: J617.1, U2401.3
UART2_TX: J616.1, U2403.4
UART_CTS_AB1532: U2402.F9, U2406.3
UART_CTS_FT234: J3101.4, J3101.6, U3103.3
UART_RTS_AB1532: U2402.F10, U2405.4
UART_RTS_FT234: J3101.2, U3102.4
UART_RX_AB1532: J2401.4, U2402.J3, U2403.3
UART_RX_FT234: J3101.10, U3105.3
UART_TX_AB1532: J2401.3, U2401.4, U2402.K3
UART_TX_FT234: J3101.8, U3104.4
USB20_DM_AG3335: CON3002.2, ESD3006.2
USB20_DM_FT234XD: C3105.2, CON3001.2, ESD3001.2, R3105.2
USB20_DP_AG3335: CON3002.3, ESD3005.2
USB20_DP_FT234XD: C3102.1, CON3001.3, ESD3002.2, R3102.2
VAUXADC: C1014.1, J1007.1, J1206.9, U1005.1
VAUXADC_IC: C409.1, J1012.7, J1206.10
VBAT: C1003.1, C1021.1, C1030.1, C1095.1, J1005.2, J1008.2, J1008.4, J1008.6, J1008.8, J1008.10, J2402.1, J9001.1, R410.2, R1036.2, R1037.2, R1040.2, R1042.2, R1043.2, R1046.2, R1048.2, R1050.2, R1052.2, SW1101.2, U1008.A2, U1012.A2, U1016.A2, U1096.8
VBAT_1V8_ADC: C1015.1, J1005.1, U1005.4
VBAT_2V8: C1028.1, J1008.7, U1010.4
VBAT_3V1_RTC: C1034.1, J1008.9, U1014.3, U1014.4
VBAT_3V3: C1006.1, J1008.5, U1002.4
VBAT_USB_1V8: C3116.1, J1008.1, U1015.7, U1015.8
VBAT_USB_3V1: C1024.1, J1008.3, U1007.4
VCCIO: C2403.2, C2421.1, U2401.6, U2402.E9, U2402.K6, U2403.1, U2405.6, U2406.1
VCCK: C414.1, J1206.16, J1206.18, Q9001.1
VCCVCO: C2419.2, U2402.K1
VCHG: C2414.1, U2402.A8
VCORE: C405.1, J1206.17
VDDIO_UART: C3104.2, C3110.2, C3112.2, C3114.2, JP3103.2, U3102.6, U3103.1, U3104.6, U3105.1
VDD_SYS_IN: C1022.1, J1206.5, L1003.2, U1008.C2
VDD_SYS_IN_IC: C411.1, J1012.5, J1206.6
VDD_VRF_IN: C1031.1, J1206.1, L1005.2, U1012.C2
VDD_VRF_IN_IC: C413.1, J1012.1, J1206.2
VIN: C2407.2, D2401.A, D2402.A, R2405.2, R2406.2, U2402.B9
VIO18: C403.1, C415.1, C416.1, F603.1, F604.1, F605.1, F606.1, J9109.1, Q9002.1, R405.2, R407.2, SW1V8.1, U1002.3, U1007.3, U1010.3
VIO18_BT: J9109.2, U2401.1, U2403.6, U2405.1, U2406.6
VRF: C404.1, J501.1, Q9003.1
VRTC: C1096.1, J1206.20, Q9005.1, U1098.1
VRTC_IN: C1099.1, J1206.7, R409.1, SW1.1, U1098.3, U1099.1
VRTC_IN_IC: C410.1, J1206.8
VRTC_PMU: C407.1, J1206.19
VSEL1: R1035.1, R1036.1, U1016.C1
VSEL2: R1037.1, R1038.1, U1016.D1
VSEL3: R1039.1, R1040.1, U1016.D2
VSEL4: R1041.1, R1042.1, U1008.C1
VSEL5: R1043.1, R1044.1, U1008.D1
VSEL6: R1045.1, R1046.1, U1008.D2
VSEL7: R1047.1, R1048.1, U1012.C1
VSEL8: R1049.1, R1050.1, U1012.D1
VSEL9: R1051.1, R1052.1, U1012.D2
VSRAM: C406.1, Q9004.1
VUSB1_5V: C3107.2, CON3001.1, ESD3003.2, J1101.2, R3002.1, R3101.1, R3103.1, U3101.4
VUSB2_5V: CON3002.1, ESD3004.2, J1102.2, R3003.1
VUSB_IN: C1019.1, J1002.1, J1206.11, U1007.1
VUSB_IN_IC: C408.1, J1206.12
V_ANT_DUAL_PWR: C506.2, C508.1, J504.3, L504.2
V_ANT_L1: C0501.1, CON501.1, L505.2
V_ANT_L1_L5: C513.1, CON503.1, L504.1
V_ANT_L5: C517.1, CON502.1, L513.2
V_ANT_SINGLE_PWR: C510.2, C511.1, C521.2, C522.1, J504.1, L505.1, L513.1
WP_SD: CON2301.10, ESD2308.2
XTAL_IN: U2402.C1, Y2401.2
XTAL_OUT: U2402.B1, Y2401.4

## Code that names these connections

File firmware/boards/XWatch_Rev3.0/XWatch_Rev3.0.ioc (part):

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Mcu.Name=STM32U5A9BJYxQ
Mcu.Package=WLCSP208
Mcu.UserName=STM32U5A9BJYxQ
PA11.GPIOParameters=GPIO_Label
PA11.GPIO_Label=USB_OTG_DM
PA11.Mode=Internal_Phy_Device
PA11.Signal=USB_OTG_HS_DM
PA12.GPIOParameters=GPIO_Label
PA12.GPIO_Label=USB_OTG_DP
PA12.Mode=Internal_Phy_Device
PA12.Signal=USB_OTG_HS_DP
PA13\ (JTMS/SWDIO).Mode=Serial_Wire
PA13\ (JTMS/SWDIO).Signal=DEBUG_JTMS-SWDIO
PA14\ (JTCK/SWCLK).Mode=Serial_Wire
PA14\ (JTCK/SWCLK).Signal=DEBUG_JTCK-SWCLK
PB10.Mode=Asynchronous
PB10.Signal=USART3_TX
PB11.Mode=Asynchronous
PB11.Signal=USART3_RX
PB12.GPIOParameters=GPIO_Label
PB12.GPIO_Label=BLE_WAKE_NRF 
PB12.Signal=GPIO_Output
PB13.Mode=CTS_RTS
PB13.Signal=USART3_CTS
PB14.Mode=CTS_RTS
PB14.Signal=USART3_RTS
PC13.GPIOParameters=GPIO_Label
PC13.GPIO_Label=BLE_WAKE_MCU
PC13.Signal=GPXTI13
PD0.GPIOParameters=GPIO_Label
PD0.GPIO_Label=PWR_EN_3V3
PD0.Signal=GPIO_Output
PD1.GPIOParameters=GPIO_Label
PD1.GPIO_Label=PWR_RIN_N
PD1.Signal=GPIO_Output
PD2.GPIOParameters=GPIO_Label
PD2.GPIO_Label=PWR_CHG_EN_N
PD2.Signal=GPIO_Output
PD3.GPIOParameters=GPIO_Label
PD3.GPIO_Label=PWR_ALRT_N
PD3.Signal=GPXTI3
PD4.GPIOParameters=GPIO_Label
PD4.GPIO_Label=PWR_INT_N
PD4.Signal=GPXTI4
PD5.GPIOParameters=GPIO_Label
PD5.GPIO_Label=DSI.RESET
PD5.Signal=GPIO_Output
PE10.Mode=O1_P1_CLK
PE10.Signal=OCTOSPIM_P1_CLK
PE11.Mode=OCTOSPI1_Port1_NCS
PE11.Signal=OCTOSPIM_P1_NCS
PE12.Mode=OCTOSPI1_IOL_Port1L
PE12.Signal=OCTOSPIM_P1_IO0
PE13.Mode=OCTOSPI1_IOL_Port1L
PE13.Signal=OCTOSPIM_P1_IO1
PE14.Mode=OCTOSPI1_IOL_Port1L
PE14.Signal=OCTOSPIM_P1_IO2
PE15.Mode=OCTOSPI1_IOL_Port1L
PE15.Signal=OCTOSPIM_P1_IO3
PE8.GPIOParameters=GPIO_Label
PE8.GPIO_Label=DSI_TP_INT
PE8.Signal=GPXTI8
PF11.Mode=DSIHost_Adapted_TE
PF11.Signal=DSIHOST_TE
PG13.Mode=I2C
PG13.Signal=I2C1_SDA
PG14.Mode=I2C
PG14.Signal=I2C1_SCL
PH0-OSC_IN\ (PH0).Mode=HSE-External-Clock-Source
PH0-OSC_IN\ (PH0).Signal=RCC_OSC_IN
PH4.Mode=I2C
PH4.Signal=I2C5_SDA
PH5.Mode=I2C
PH5.Signal=I2C5_SCL
PH7.Mode=I2C
PH7.Signal=I2C3_SCL
PH8.Mode=I2C
PH8.Signal=I2C3_SDA
PI5.GPIOParameters=GPIO_Label
PI5.GPIO_Label=DSI_PWR_EN
PI5.Signal=GPIO_Output
PI6.GPIOParameters=GPIO_Label
PI6.GPIO_Label=DSI_TP_RESET
PI6.Signal=GPIO_Output
RCC.HSE_VALUE=16000000
RCC.SYSCLKFreq_VALUE=160000000
RCC.SYSCLKSource=RCC_SYSCLKSOURCE_PLLCLK
board=custom
